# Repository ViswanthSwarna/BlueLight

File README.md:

# 11 LED MCPCB

KiCad project for an aluminum-core LED board:

- Board size: 50 mm x 50 mm square
- Mounting: 4x M3 non-plated holes, 40 mm x 40 mm pattern
- LED layout: 11 LEDs in 3 rows, arranged 3 / 4 / 4
- Electrical layout: one series string from `VIN+` to `VIN-`
- LED pad geometry follows the supplied drawing: two 0.55 mm x 1.35 mm SMD pads with a 0.25 mm gap

Manufacturing notes:

- Order as aluminum PCB / MCPCB, single-sided copper.
- Confirm the LED package and current before fabrication. The footprint matches the provided solder-pad drawing, but LED polarity and package height should be checked against the exact LED datasheet.
- Use thermal paste or a thermal pad between the MCPCB and heat sink.
- The 50 mm square / 40 mm mounting pattern is intentionally conservative so it can be mounted to common small LED or electronics heat sinks.

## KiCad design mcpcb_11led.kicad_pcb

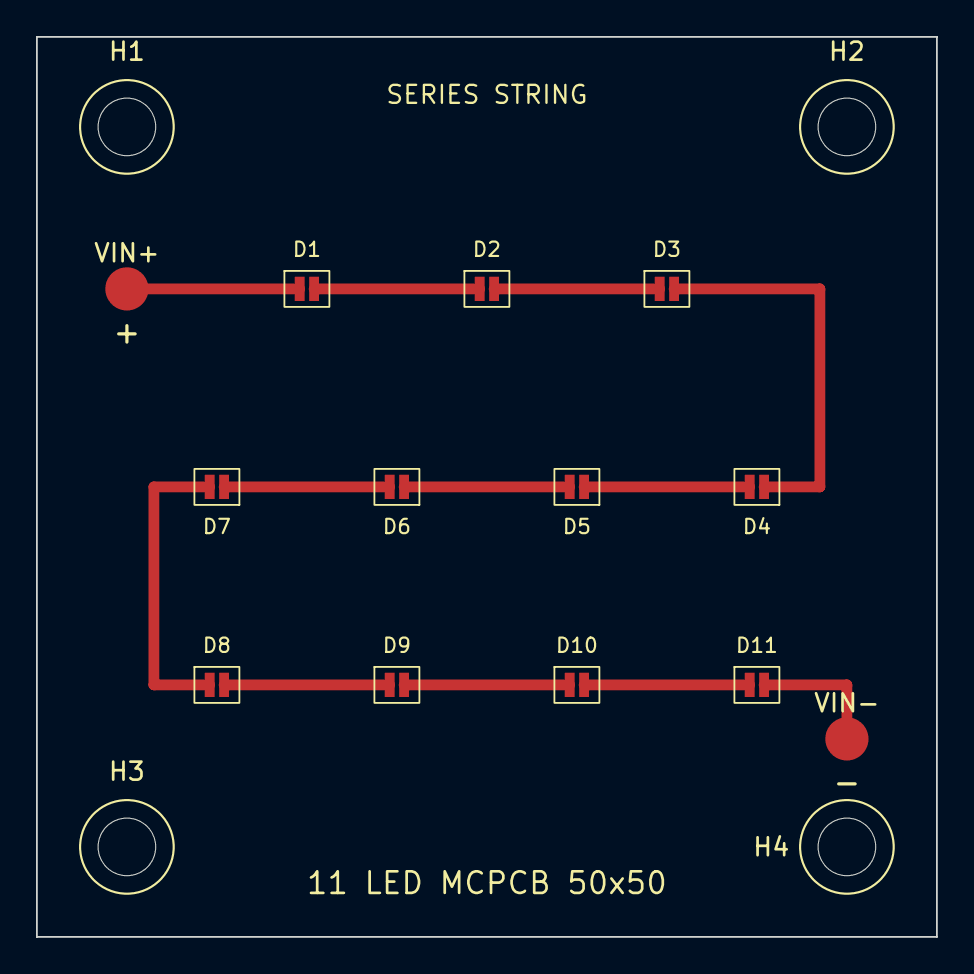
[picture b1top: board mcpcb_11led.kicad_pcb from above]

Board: 2 copper layers, 50.0 x 50.0 mm, 17 parts (0 on the bottom side), 12 nets.

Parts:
D1, D2, D3, D4, D5, D6, D7, D8, D9, D10, D11: LED; LED_0.55x1.35_gap0.25
H1, H2, H3, H4: M3; MountingHole_3.2mm_M3
VIN+: SOLDER_PAD; VIN_PLUS
VIN-: SOLDER_PAD; VIN_MINUS

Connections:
N1: D1.K, D2.A
N2: D2.K, D3.A
N3: D3.K, D4.A
N4: D4.K, D5.A
N5: D5.K, D6.A
N6: D6.K, D7.A
N7: D7.K, D8.A
N8: D8.K, D9.A
N9: D9.K, D10.A
N10: D10.K, D11.A
VIN+: D1.A, VIN+.1
VIN-: D11.K, VIN-.1

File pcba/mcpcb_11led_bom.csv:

Comment,Designator,Footprint,LCSC Part #,Manufacturer,Manufacturer Part Number,Quantity
"OSLON Pure 1414, 488 nm LED","D1,D2,D3,D4,D5,D6,D7,D8,D9,D10,D11","LED_Custom:LED_0.55x1.35_gap0.25","","ams OSRAM","GC VJLPL1.13-KQKS-V2V3-1",11
